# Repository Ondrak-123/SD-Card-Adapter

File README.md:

# SD Card Adapter
---
## Introduction
**- This is an SD + micro SD card to USB A adapter, that supports USB 2.0.**
#### **Parts, usage, description:**
- The main chip for this project will be GL823K from Genesys Logic, that supports USB 2.0 (High-Speed 480 Mbps), this chip is great thanks to its simplicity since it has integrated 5V to 3V3, 3V3 to 1V8 regulators and it also has a crystal integrated so no external crystal or timing capacitors needed. (The datasheet for this can be found at alldatasheet.com.
- LED included to show its status.
- All of the data lines D0-D3 and CMD needs to have pull ups (10K to 3V3), (excluding CLK).
- Decoupling capacitors 100nF for each power pin on the IC (VDD, VDDA).
- Mosfet for powering the SD cards.
- A protection circuit that cuts off power to the other SD card if both are plugged in.
- 4 Layer Board, (Each layer having a ground pour). First layer (Top): Signals, Data lines, Second layer (Inner1): pure ground, no normal traces, Third layer (Inner2): power, 5V, 3,3V and nets like SDPWR, BIGSDPWR, Fourth layer (Bottom): signal traces that did not fit on the first layer, and everything else that didnt fit on top.
- Each data line (D+, D-) should have impedance of around 90R, also the traces should be the same width, lenght and spacing.

## Schematic:

## PCB:

## 3D Rendering:

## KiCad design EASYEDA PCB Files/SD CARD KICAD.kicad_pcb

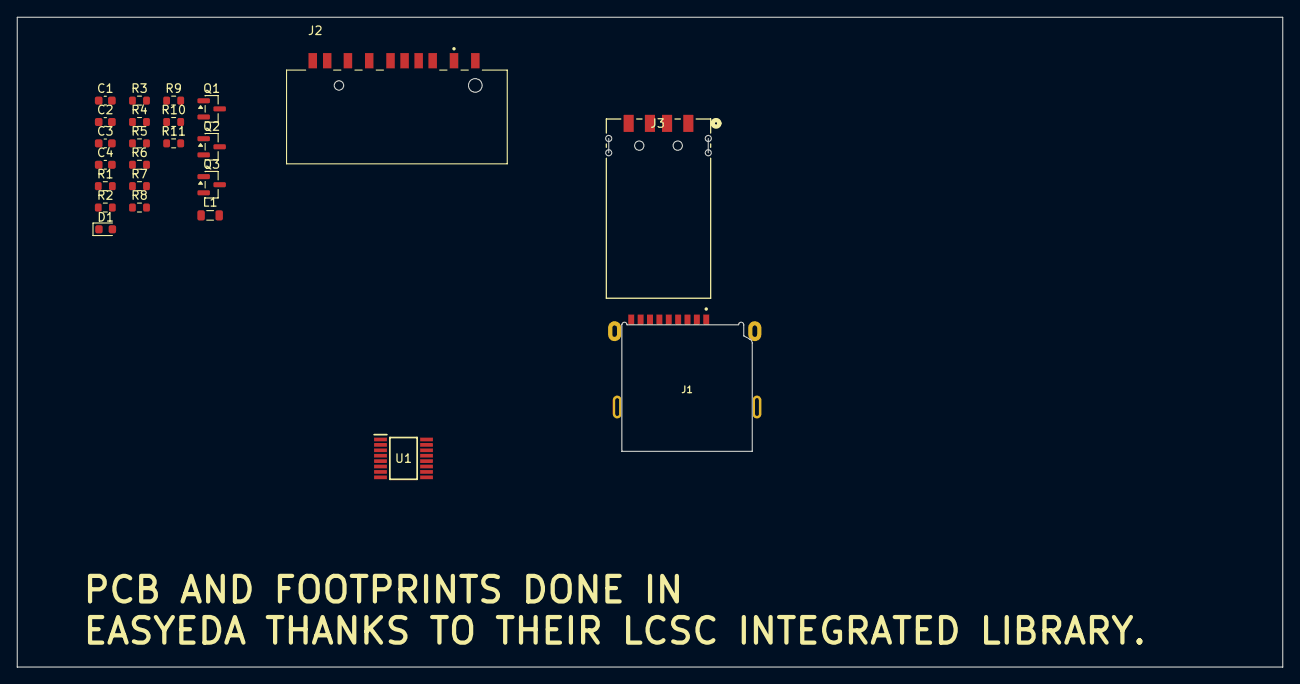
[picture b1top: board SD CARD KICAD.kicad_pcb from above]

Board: 2 copper layers, 148.5 x 76.2 mm, 24 parts (0 on the bottom side), 21 nets, no tracks yet.

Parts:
C1: 4.7uF; C_0603_1608Metric
C2: 10uF; C_0603_1608Metric
C3, C4: 100nF; C_0603_1608Metric
D1: LED; LED_0603_1608Metric
J1: Micro_SD_Card_Det1; CUI_MSD-3-A
J2: SD_Card_Receptacle; CUI_SD-6-B
J3: USB_A; CONN_48037-2100_MOL
L1: 600R 100MHz; L_0805_2012Metric
Q1, Q3: AO3401A; SOT-23
Q2: 2N7002; SOT-23
R1, R2: 27R; R_0603_1608Metric
R3, R4, R5, R6, R7, R8, R9, R10: 10K; R_0603_1608Metric
R11: 470R; R_0603_1608Metric
U1: GL823K-HCY04; SOP64P600X175-16N

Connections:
+3.3V: C2.1, C3.1, C4.1, Q1.2 (S), R3.1, R4.1, R5.1, R6.1, R7.1, R10.1, U1.9 (VDD), U1.13 (VDDA)
+5V: C1.1, L1.2, U1.10 (5V)
BIGSDPWR: J2.4 (VDD), Q3.3 (D)
CLK: J1.5 (CLK), J2.5 (CLK), U1.4 (CLK)
CMD: J1.3 (CMD), J2.2 (CMD), R5.2, U1.5 (CMD)
D0: J1.7 (DAT0), J2.7 (DAT0), R4.2, U1.3 (D0)
D1: J1.8 (DAT1), J2.8 (DAT1), R3.2, U1.2 (D1)
D2: J1.1 (DAT2), J2.9 (DAT2), R7.2, U1.7 (D2)
D3: J1.2 (DAT3/CD), J2.1 (CD/DAT3), R6.2, U1.6 (D3)
DET: Q2.1 (G), R8.2
DM: R2.2, U1.16 (DM)
DP: R1.2, U1.15 (DP)
GND: C1.2, C2.2, C3.2, C4.2, D1.1 (K), J1.6 (VSS), J2.3 (VSS), J2.6 (VSS), J2.CD, J3.4 (GND), Q2.2 (S), U1.1 (VSS), U1.14 (VSS)
LED: R11.1, U1.12 (LED)
unnamed: D1.2 (A), R11.2
unnamed: J3.3 (D+), R1.1
unnamed: J3.2 (D-), R2.1
unnamed: J3.1 (VBUS), L1.1
unnamed: Q2.3 (D), Q3.1 (G), R9.2
PMOS: Q1.1 (G), R10.2, U1.8 (PMOS)
SDPWR: J1.4 (VDD), Q1.3 (D), Q3.2 (S), R8.1, R9.1

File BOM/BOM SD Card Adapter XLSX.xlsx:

No. | Quantity | Comment | Designator | Footprint | Value | Manufacturer Part | Manufacturer | Supplier Part | Supplier | Total price (USD) $
1 | 1 | 4.7uF | C1 | Capacitor_SMD:C_0603_1608Metric | 4.7uF |  |  | C69335 | LCSC | 0.49
2 | 1 | 10uF | C2 | Capacitor_SMD:C_0603_1608Metric | 10uF |  |  | C962136 | LCSC | 0.43
3 | 2 | 100nF | C3,C4 | Capacitor_SMD:C_0603_1608Metric | 100nF | CL10B104KO8NNNC | SAMSUNG(三星) | C66501 | LCSC | 0.73
4 | 1 | XKSD-013 | CARD1 | SIM-SMD_XKSD-013 |  | XKSD-013 | XKB Connection(中国星坤) | C2764609 | LCSC | 0.83
5 | 1 | TF PUSH | CARD2 | TF-SMD_TF-PUSH |  | TF PUSH | SHOU HAN(首韩) | C393941 | LCSC | 0.65
6 | 1 | YLED0603B | D1 | LED_SMD:LED_0603_1608Metric |  | YLED0603B | YONGYUTAI(永裕泰) | C19171394 | LCSC | 0.61
7 | 1 | MPZ2012S601AT000 | L1 | Inductor_SMD:L_0805_2012Metric |  | MPZ2012S601AT000 | TDK | C21519 | LCSC | 0.26
8 | 2 | AO3401A | Q1,Q3 | Package_TO_SOT_SMD:SOT-23 |  | AO3401A | baocheng(宝乘) | C48678024 | LCSC | 0.62
9 | 1 | 2N7002 | Q2 | Package_TO_SOT_SMD:SOT-23 |  | 2N7002 | JSMSEMI(杰盛微) | C916396 | LCSC | 0.44
10 | 2 | 27Ω | R1,R2 | Resistor_SMD:R_0603_1608Metric | 27Ω | RC0603FR-0727RL | YAGEO(国巨) | C137753 | LCSC | 0.2
11 | 8 | 10kΩ | R3,R4,R5,R6,R7,R8,R9,R10 | Resistor_SMD:R_0603_1608Metric | 10kΩ | FRC0603J103 TS | FOJAN(富捷) | C2930027 | LCSC | 0.13
12 | 1 | 470Ω | R11 | Resistor_SMD:R_0603_1608Metric | 470Ω | FRC0603J471 TS | FOJAN(富捷) | C2907172 | LCSC | 0.18
13 | 1 | GL823K-HCY04 | U2 | SSOP-16_L4.9-W3.9-P0.64-LS6.0-BL |  | GL823K-HCY04 | GENESYS(创惟) | C284879 | LCSC | 0.46
14 | 1 | USB-212-BCW | USB1 | USB-A-SMD_USB-212-BCW |  | USB-212-BCW | XUNPU(讯普) | C720521 | LCSC | 0.54
15 | 1 | PCB |  |  |  |  | JLPCB |  |  | 4.24
16 |  | LCSC Shipping |  |  |  |  | LCSC |  |  | 10.35
 |  | LCSC Handling fee |  |  |  |  |  |  |  | 3
 |  |  |  |  |  |  |  |  |  | 24.16
 |  |  |  |  |  |  |  |  | Total: | 25 $ USD
 |  |  |  |  |  |  |  |  |  | ’+28$ EU CFF
 |  |  |  |  |  |  |  |  | Requesting amount: | 55$
 |  |  |  |  | The whole LCSC cart can be downloaded on the Github. (So you can see and add al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
 |  |  |  |  | Since 1. July 2026 there will be a new Category Flat Fee, affecting all EU resi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
 |  |  |  |  | fee of 3€, the HS Codes for this package are: HS853224, HS853321, HS853400, HS8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
 |  |  |  |  | Which is 8*3€ or 24€ (28$). This fee will be added automatically when
 |  |  |  |  | checking out (starting on 1.7.2026). But if I order a package on the 20.6. and 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
 |  |  |  |  | still need to pay the fees. THIS IS NOT A LOCAL/POST OR A COUNTRY FEE!!!

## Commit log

2026-05-30 Import
2026-05-30 added fusion files
2026-05-30 readme updated
2026-06-20 Delete
